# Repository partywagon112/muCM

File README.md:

# μCM

A small ESP32 based flexible controller, intended for Matter to control an RGB light or motor, but very very flexible. Based around ESP32-C6 for flexibility. Built to work in two contexts, in isolated locations where only power may be provided, up to 40V 3A, or as a PD powered dongle, up to 20V, 3A. 

Includes a 3V3 CAN driver for interacting with smaller devices, two pairs of half bridges allow driving servos, LEDs, or outputs more generally.

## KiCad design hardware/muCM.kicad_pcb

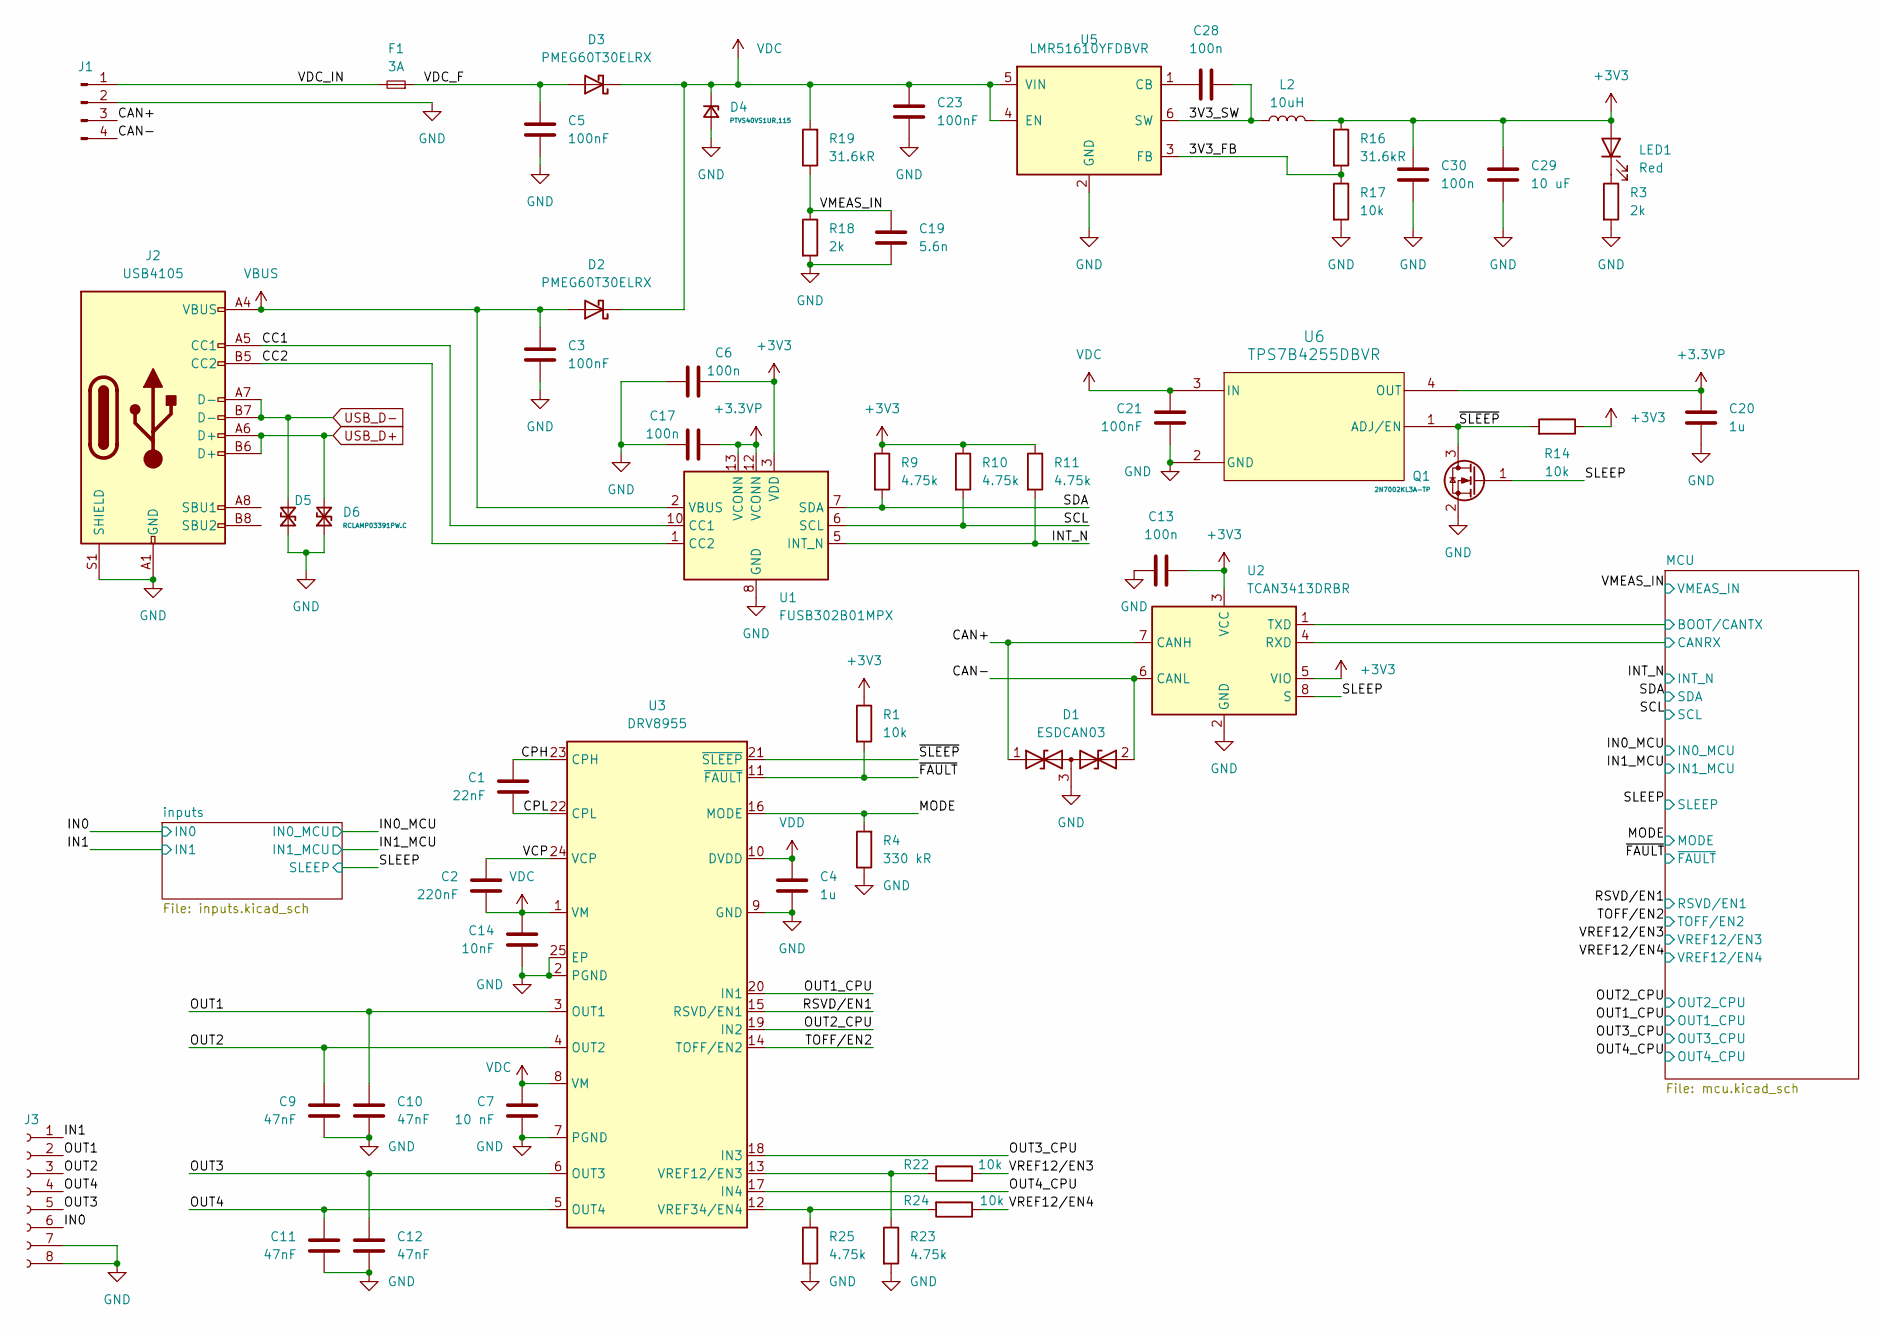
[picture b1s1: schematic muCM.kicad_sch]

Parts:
C1: 22nF; C_0603_1608Metric; MPN CL10B223KC8WPNC; DigiKey SPN 1276-CL10B223KC8WPNCCT-ND
C2: 220nF; C_0603_1608Metric; MPN HMK107C7224MAHTE; DigiKey SPN 587-5013-1-ND
C3, C5, C21, C23: 100nF; C_0603_1608Metric; MPN GCJ188R72A104KA01D; DigiKey SPN 490-13420-1-ND
C4, C20: 1u; C_0603_1608Metric; MPN GRT188R61H105KE13D; DigiKey SPN 490-12330-1-ND
C6, C13, C17, C28, C30: 100n; C_0402_1005Metric; MPN GCM155R71H104KE02J
C7: 10 nF; R_0603_1608Metric; MPN GCM188R71H103KA37D; DigiKey SPN 490-4778-1-ND
C9, C10, C11, C12: 47nF; C_0603_1608Metric; MPN CGA3E3X7S2A473K080AE; DigiKey SPN 445-173702-1-ND
C14: 10nF; C_0603_1608Metric; MPN CL10B103KC8WPNC; DigiKey SPN 1276-6556-1-ND
C19: 5.6n; C_0402_1005Metric; MPN GCM155R71H562KA55D; DigiKey SPN 490-GCM155R71H562KA55DCT-ND
C29: 10 uF; C_0603_1608Metric; MPN GRT188R61E106ME13D; DigiKey SPN 490-12323-1-ND
D1: ESDCAN03; DFN1006-3; MPN ESDCAN03-2BM3Y; DigiKey SPN 497-ESDCAN03-2BM3YCT-ND
D2, D3: PMEG60T30ELRX; Nexperia_CFP3_SOD-123W; MPN PMEG60T30ELRX; DigiKey SPN 1727-7806-1-ND
D4: PTVS40VS1UR,115; Nexperia_CFP3_SOD-123W; MPN PTVS40VS1UR,115; DigiKey SPN 1727-5873-1-ND
D5, D6: RCLAMP03391PW.C; D_SOD-882; MPN RCLAMP03391PW.C; DigiKey SPN 600-RCLAMP03391PW.CCT-ND
F1: 3A; Fuse_0805_2012Metric; MPN MFU0805FF03000P100; DigiKey SPN MFU08053.00CT-ND
J1: CDM806-04A-MP-F011-67; CUI_CDM806-04A-MP-F011-67; MPN CDM806-04A-MP-F011-67; DigiKey SPN 2223-CDM806-04A-MP-F011-67-ND
J2: USB4105; USB_C_Receptacle_GCT_USB4105-xx-A_16P_TopMnt_Horizontal; MPN USB4105-GF-A; DigiKey SPN 2073-USB4105-GF-ACT-ND
J3: CDM805-08A-FP-F011-67; CUI_CDM805-08A-FP-F011-67; MPN CDM805-08A-FP-F011-67; DigiKey SPN 2223-CDM805-08A-FP-F011-67-ND
L2: 10uH; L_1008_2520Metric; MPN SRN2510BTA-100M; DigiKey SPN 118-SRN2510BTA-100MCT-ND
LED1: Red; LED_0603_1608Metric; MPN 150060SS75020
Q1: 2N7002KL3A-TP; Diodes_DFN1006-3; MPN 2N7002KL3A-TP; DigiKey SPN 353-2N7002KL3A-TPCT-ND
R1, R14, R17, R22, R24: 10k; R_0402_1005Metric; MPN CR0402AFX-1002GAS; DigiKey SPN CR0402AFX-1002GASCT-ND
R3, R18: 2k; R_0402_1005Metric; MPN CR0402AFX-2001GAS
R4: 330 kR; R_0402_1005Metric; MPN CRGCQ0402F330K; DigiKey SPN A129657CT-ND
R9, R10, R11, R23, R25: 4.75k; R_0402_1005Metric; MPN CR0402AFX-4751GAS; DigiKey SPN CR0402AFX-4751GASCT-ND
R16, R19: 31.6kR; R_0402_1005Metric; MPN CRCW040231K6FKED; DigiKey SPN 541-31.6KLCT-ND
U1: FUSB302B01MPX; WQFN-14-1EP_2.5x2.5mm_P0.5mm_EP1.45x1.45mm; MPN FUSB302B01MPX; DigiKey SPN FUSB302B01MPXCT-ND
U2: TCAN3413DRBR; VSON-8-1EP_3x3mm_P0.65mm_EP1.6x2.4mm; MPN TCAN3413DRBR; DigiKey SPN 296-TCAN3413DRBRCT-ND
U3: DRV8955; VQFN-24-1EP_4x4mm_P0.5mm_EP2.45x2.45mm; MPN DRV8955PRGER; DigiKey SPN 296-DRV8955PRGERCT-ND
U5: LMR51610YFDBVR; SOT-23-6; MPN LMR51610YFDBVR; DigiKey SPN 296-LMR51610YFDBVRCT-ND
U6: TPS7B4255DBVR; SOT-23-5; MPN TPS7B4255DBVR; DigiKey SPN 296-TPS7B4255DBVRCT-ND

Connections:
+3.3VP: C17.1, C20.1, U1.12 (VCONN), U1.13 (VCONN), U6.4 (OUT); also elsewhere on the board
+3V3: C6.1, C13.2, C29.1, C30.1, L2.2, LED1.2 (A), R1.1, R9.1, R10.1, R11.1, R14.1, R16.1, U1.3 (VDD), U1.4 (VDD), U2.3 (VCC), U2.5 (VIO); also elsewhere on the board
/3V3_FB: R16.2, R17.1, U5.3 (FB)
/3V3_SW: C28.2, L2.1, U5.6 (SW)
/CAN+: D1.1 (A1), J1.3, U2.7 (CANH)
/CAN-: D1.2 (A2), J1.4, U2.6 (CANL)
/CC1: J2.A5 (CC1), U1.10 (CC1), U1.11 (CC1)
/CC2: J2.B5 (CC2), U1.1 (CC2), U1.14 (CC2)
/CPH: C1.1, U3.23 (CPH)
/CPL: C1.2, U3.22 (CPL)
/IN0: J3.6; also elsewhere on the board
/IN1: J3.1; also elsewhere on the board
/INT_N: R11.2, U1.5 (INT_N); also elsewhere on the board
/MCU/BOOT/CANTX: U2.1 (TXD); also elsewhere on the board
/MCU/CANRX: U2.4 (RXD); also elsewhere on the board
/MODE: R4.2, U3.16 (MODE); also elsewhere on the board
/OUT1: C10.1, J3.2, U3.3 (OUT1)
/OUT1_CPU: U3.20 (IN1); also elsewhere on the board
/OUT2: C9.1, J3.3, U3.4 (OUT2)
/OUT2_CPU: U3.19 (IN2); also elsewhere on the board
/OUT3: C12.1, J3.5, U3.6 (OUT3)
/OUT3_CPU: U3.18 (IN3); also elsewhere on the board
/OUT4: C11.1, J3.4, U3.5 (OUT4)
/OUT4_CPU: U3.17 (IN4); also elsewhere on the board
/RSVD/EN1: U3.15 (RSVD/EN1); also elsewhere on the board
/SCL: R10.2, U1.6 (SCL); also elsewhere on the board
/SDA: R9.2, U1.7 (SDA); also elsewhere on the board
/SLEEP: Q1.1 (G), U2.8 (S); also elsewhere on the board
/TOFF/EN2: U3.14 (TOFF/EN2); also elsewhere on the board
/VCP: C2.1, U3.24 (VCP)
/VDC_F: C5.1, D3.2 (A), F1.1
/VDC_IN: F1.2, J1.1
/VMEAS_IN: C19.1, R18.1, R19.1; also elsewhere on the board
/VREF12/EN3: R22.2; also elsewhere on the board
/VREF12/EN4: R24.1; also elsewhere on the board
/~FAULT: R1.2, U3.11 (~FAULT); also elsewhere on the board
/~SLEEP: Q1.3 (D), R14.2, U3.21 (~SLEEP), U6.1 (ADJ/EN)
GND: C3.2, C4.2, C5.2, C6.2, C7.2, C9.2, C10.2, C11.2, C12.2, C13.1, C14.2, C17.2, C19.2, C20.2, C21.2, C23.2, C29.2, C30.2, D1.3 (common), D4.2 (A), D5.1 (A1), D6.1 (A1), J1.2, J2.A1 (GND), J2.A12 (GND), J2.B1 (GND), J2.B12 (GND), J2.S1 (SHIELD), J3.7, J3.8, Q1.2 (S), R3.2, R4.1, R17.2, R18.2, R23.2, R25.2, U1.8 (GND), U1.9 (GND), U1.15 (GND), U2.2 (GND), U2.9, U3.2 (PGND), U3.7 (PGND), U3.9 (GND), U3.25 (EP), U5.2 (GND), U6.2 (GND); also elsewhere on the board
unnamed: LED1.1 (K), R3.1
unnamed: R22.1, R23.1, U3.13 (VREF12/EN3)
unnamed: R24.2, R25.1, U3.12 (VREF34/EN4)
unnamed: C28.1, U5.1 (CB)
USB_D+: D6.2 (A2), J2.A6 (D+), J2.B6 (D+); also elsewhere on the board
USB_D-: D5.2 (A2), J2.A7 (D-), J2.B7 (D-); also elsewhere on the board
VBUS: C3.1, D2.2 (A), J2.A4 (VBUS), J2.A9 (VBUS), J2.B4 (VBUS), J2.B9 (VBUS), U1.2 (VBUS)
VDC: C2.2, C7.1, C14.1, C21.1, C23.1, D2.1 (K), D3.1 (K), D4.1 (K), R19.2, U3.1 (VM), U3.8 (VM), U5.4 (EN), U5.5 (VIN), U6.3 (IN)
VDD: C4.1, U3.10 (DVDD)

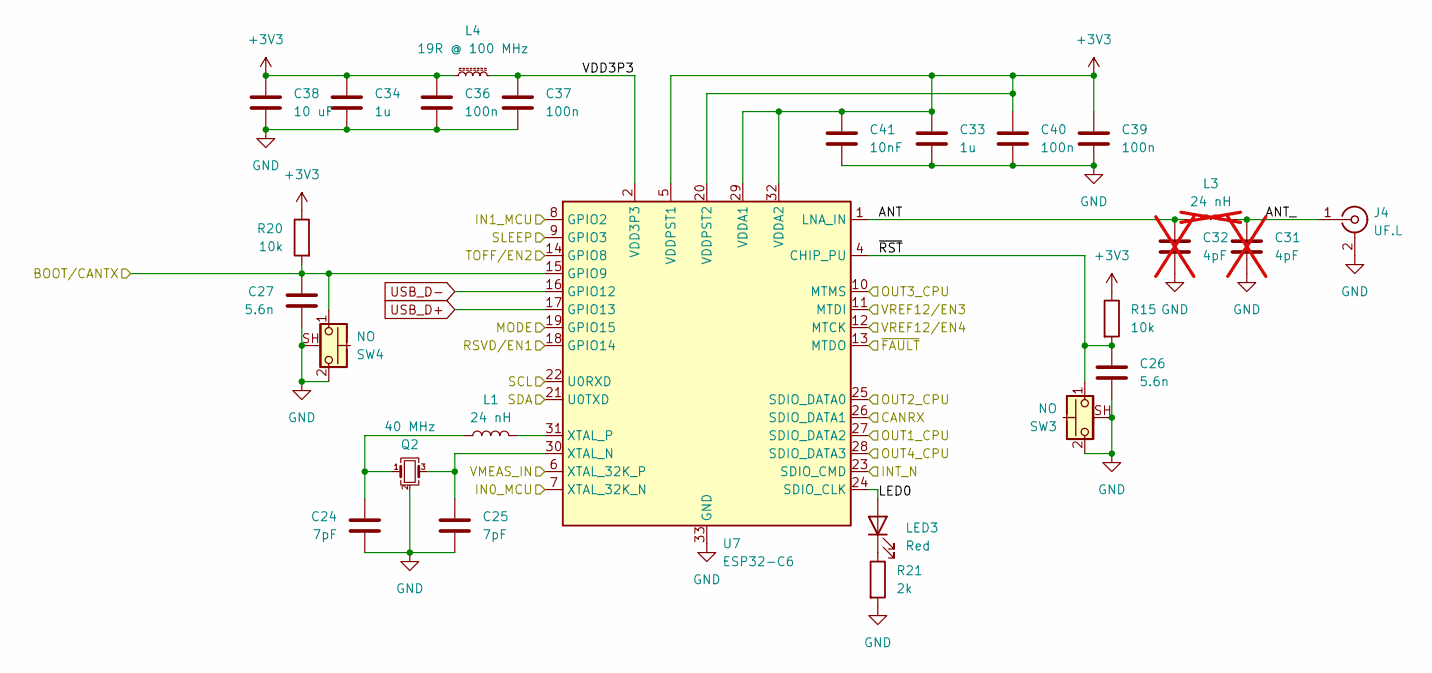
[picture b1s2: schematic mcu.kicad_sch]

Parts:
C24, C25: 7pF; C_0402_1005Metric; MPN GCM1555C1H7R0BA16D; DigiKey SPN 490-GCM1555C1H7R0BA16DCT-ND
C26, C27: 5.6n; C_0402_1005Metric; MPN GCM155R71H562KA55D; DigiKey SPN 490-GCM155R71H562KA55DCT-ND
C31, C32: 4pF; C_0402_1005Metric; MPN GCM1555C1H4R0BA16D; DigiKey SPN 490-GCM1555C1H4R0BA16DCT-ND; not fitted
C33, C34: 1u; C_0603_1608Metric; MPN GRT188R61H105KE13D; DigiKey SPN 490-12330-1-ND
C36, C37, C39, C40: 100n; C_0402_1005Metric; MPN GCM155R71H104KE02J
C38: 10 uF; C_0603_1608Metric; MPN GRT188R61E106ME13D; DigiKey SPN 490-12323-1-ND
C41: 10nF; C_0402_1005Metric; MPN GCM155R71H103KA55D; DigiKey SPN 490-4762-1-ND
J4: UF.L; U.FL_Hirose_U.FL-R-SMT-1_Vertical; MPN U.FL-R-SMT(10); DigiKey SPN H9161CT-ND
L1: 24 nH; L_0402_1005Metric; MPN MLG1005S24NJTD25; DigiKey SPN 445-16275-1-ND
L3: 24 nH; L_0402_1005Metric; MPN MLG1005S24NJTD25; DigiKey SPN 445-16275-1-ND; not fitted
L4: 19R @ 100 MHz; L_0402_1005Metric; MPN LI0402E190R-10; DigiKey SPN 240-LI0402E190R-10CT-ND
LED3: Red; LED_0603_1608Metric; MPN 150060SS75020
Q2: 40 MHz; Crystal_SMD_2016-4Pin_2.0x1.6mm; MPN XTL501100-M118-207; DigiKey SPN 3994-XTL501100-M118-207CT-ND
R15, R20: 10k; R_0402_1005Metric; MPN CR0402AFX-1002GAS; DigiKey SPN CR0402AFX-1002GASCT-ND
R21: 2k; R_0402_1005Metric; MPN CR0402AFX-2001GAS
SW3, SW4: NO; SW_Push_1P1T-SH_NO_CK_KMR2xxG; MPN KMR221G LFS; DigiKey SPN 401-1427-1-ND
U7: ESP32-C6; QFN-32-1EP_5x5mm_P0.5mm_EP3.7x3.7mm; MPN ESP32-C6FH4; DigiKey SPN 1904-ESP32-C6FH4CT-ND

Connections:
+3V3: C33.1, C34.1, C36.1, C38.1, C39.1, C40.1, C41.1, L4.1, R15.1, R20.1, U7.5 (VDDPST1), U7.20 (VDDPST2), U7.29 (VDDA1), U7.32 (VDDA2); also elsewhere on the board
/IN0_MCU: U7.7 (XTAL_32K_N); also elsewhere on the board
/IN1_MCU: U7.8 (GPIO2); also elsewhere on the board
/INT_N: U7.23 (SDIO_CMD); also elsewhere on the board
/MCU/ANT: C32.1, L3.1, U7.1 (LNA_IN)
/MCU/ANT_: C31.1, J4.1 (In), L3.2
/MCU/BOOT/CANTX: C27.1, R20.2, SW4.1, U7.15 (GPIO9); also elsewhere on the board
/MCU/CANRX: U7.26 (SDIO_DATA1); also elsewhere on the board
/MCU/LED0: LED3.2 (A), U7.24 (SDIO_CLK)
/MCU/~RST: C26.1, R15.2, SW3.1, U7.4 (CHIP_PU)
/MODE: U7.19 (GPIO15); also elsewhere on the board
/OUT1_CPU: U7.27 (SDIO_DATA2); also elsewhere on the board
/OUT2_CPU: U7.25 (SDIO_DATA0); also elsewhere on the board
/OUT3_CPU: U7.10 (MTMS); also elsewhere on the board
/OUT4_CPU: U7.28 (SDIO_DATA3); also elsewhere on the board
/RSVD/EN1: U7.18 (GPIO14); also elsewhere on the board
/SCL: U7.22 (U0RXD); also elsewhere on the board
/SDA: U7.21 (U0TXD); also elsewhere on the board
/SLEEP: U7.9 (GPIO3); also elsewhere on the board
/TOFF/EN2: U7.14 (GPIO8); also elsewhere on the board
/VMEAS_IN: U7.6 (XTAL_32K_P); also elsewhere on the board
/VREF12/EN3: U7.11 (MTDI); also elsewhere on the board
/VREF12/EN4: U7.12 (MTCK); also elsewhere on the board
/~FAULT: U7.13 (MTDO); also elsewhere on the board
GND: C24.2, C25.2, C26.2, C27.2, C31.2, C32.2, C33.2, C34.2, C36.2, C37.2, C38.2, C39.2, C40.2, C41.2, J4.2 (Ext), Q2.2 (G), Q2.4 (G), R21.2, SW3.2, SW3.SH (B), SW4.2, SW4.SH (B), U7.33 (GND); also elsewhere on the board
unnamed: C24.1, L1.1, Q2.1
unnamed: LED3.1 (K), R21.1
unnamed: C25.1, Q2.3, U7.30 (XTAL_N)
unnamed: L1.2, U7.31 (XTAL_P)
USB_D+: U7.17 (GPIO13); also elsewhere on the board
USB_D-: U7.16 (GPIO12); also elsewhere on the board
VDD3P3: C37.1, L4.2, U7.2 (VDD3P3), U7.3 (VDD3P3)

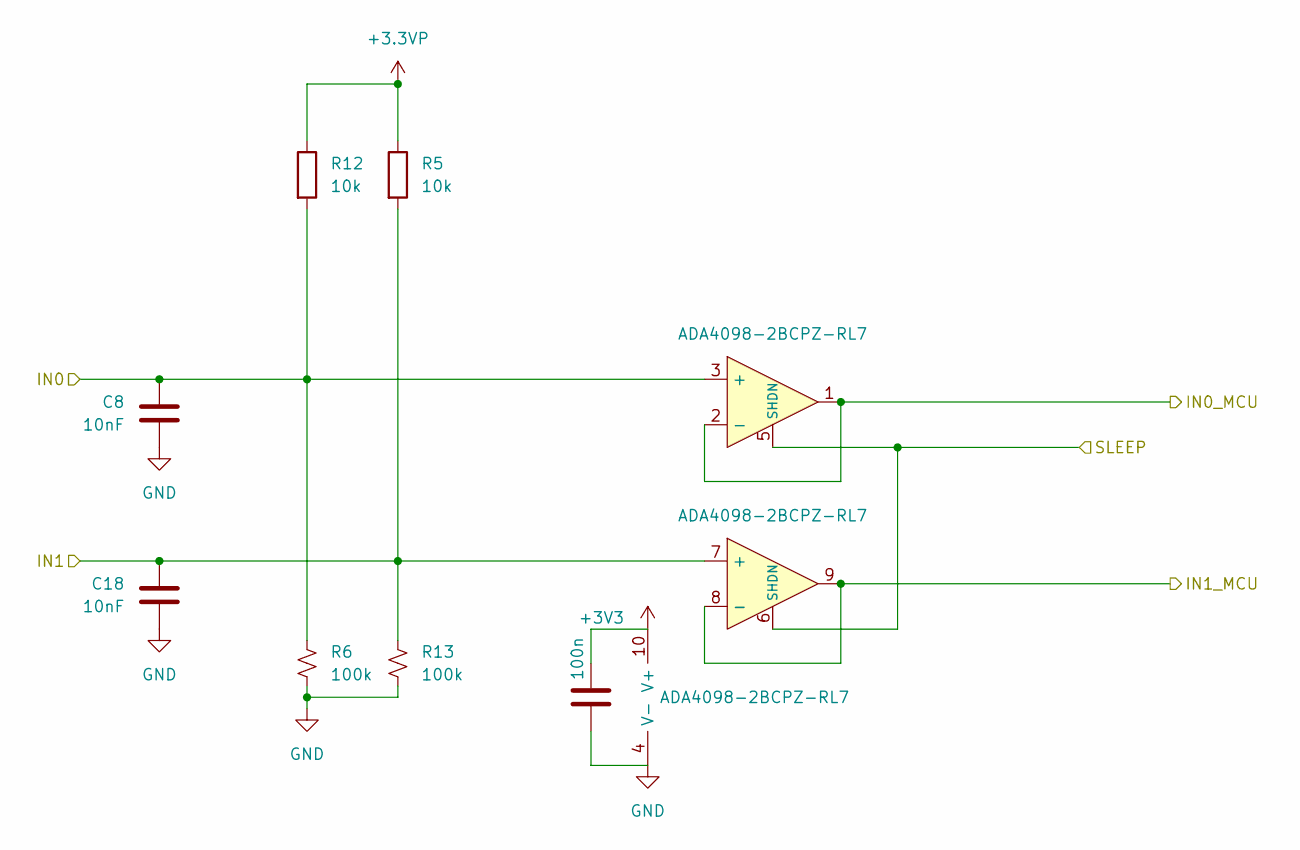
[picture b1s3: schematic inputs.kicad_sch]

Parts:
C8, C18: 10nF; C_0603_1608Metric; MPN CL10B103KC8WPNC; DigiKey SPN 1276-6556-1-ND
C22: 100n; C_0402_1005Metric; MPN GCM155R71H104KE02J
R5, R12: 10k; R_0402_1005Metric; MPN CR0402AFX-1002GAS; DigiKey SPN CR0402AFX-1002GASCT-ND
R6, R13: 100k; R_0402_1005Metric
U4: ADA4098-2BCPZ-RL7; LFCSP-WD-10-1EP_3x3mm_P0.5mm_EP1.64x2.38mm; MPN ADA4098-2BCPZ-RL7; DigiKey SPN 505-ADA4098-2BCPZ-RL7TR-ND

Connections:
+3.3VP: R5.1, R12.1; also elsewhere on the board
+3V3: C22.1, U4.10 (V+); also elsewhere on the board
/IN0: C8.1, R6.2, R12.2, U4.3 (+); also elsewhere on the board
/IN0_MCU: U4.1, U4.2 (-); also elsewhere on the board
/IN1: C18.1, R5.2, R13.2, U4.7 (+); also elsewhere on the board
/IN1_MCU: U4.8 (-), U4.9; also elsewhere on the board
/SLEEP: U4.5 (SHDN), U4.6 (SHDN); also elsewhere on the board
GND: C8.2, C18.2, C22.2, R6.1, R13.1, U4.4 (V-), U4.11 (V-); also elsewhere on the board

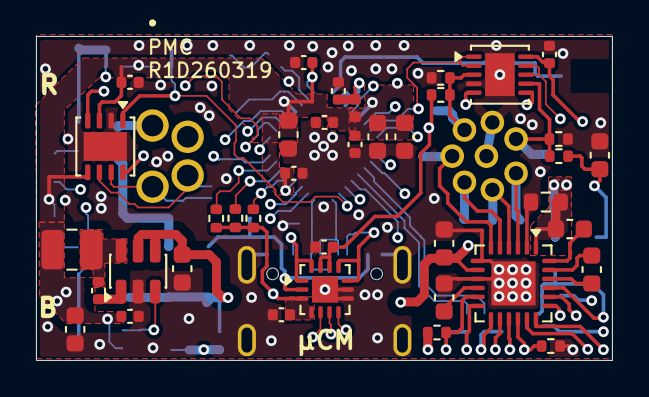
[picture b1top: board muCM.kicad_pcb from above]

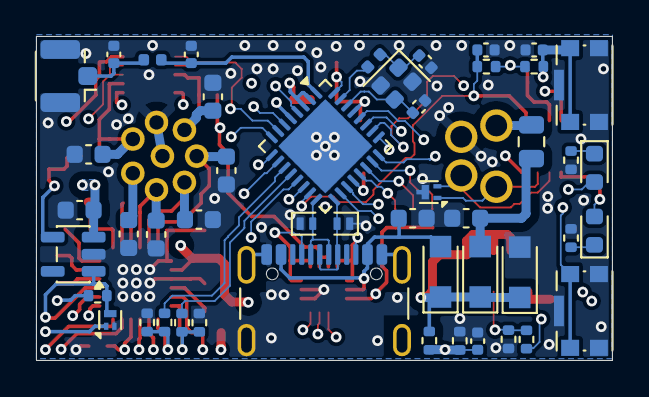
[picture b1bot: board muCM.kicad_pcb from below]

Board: 4 copper layers, 32.0 x 18.0 mm, 88 parts (48 on the bottom side), 58 nets.

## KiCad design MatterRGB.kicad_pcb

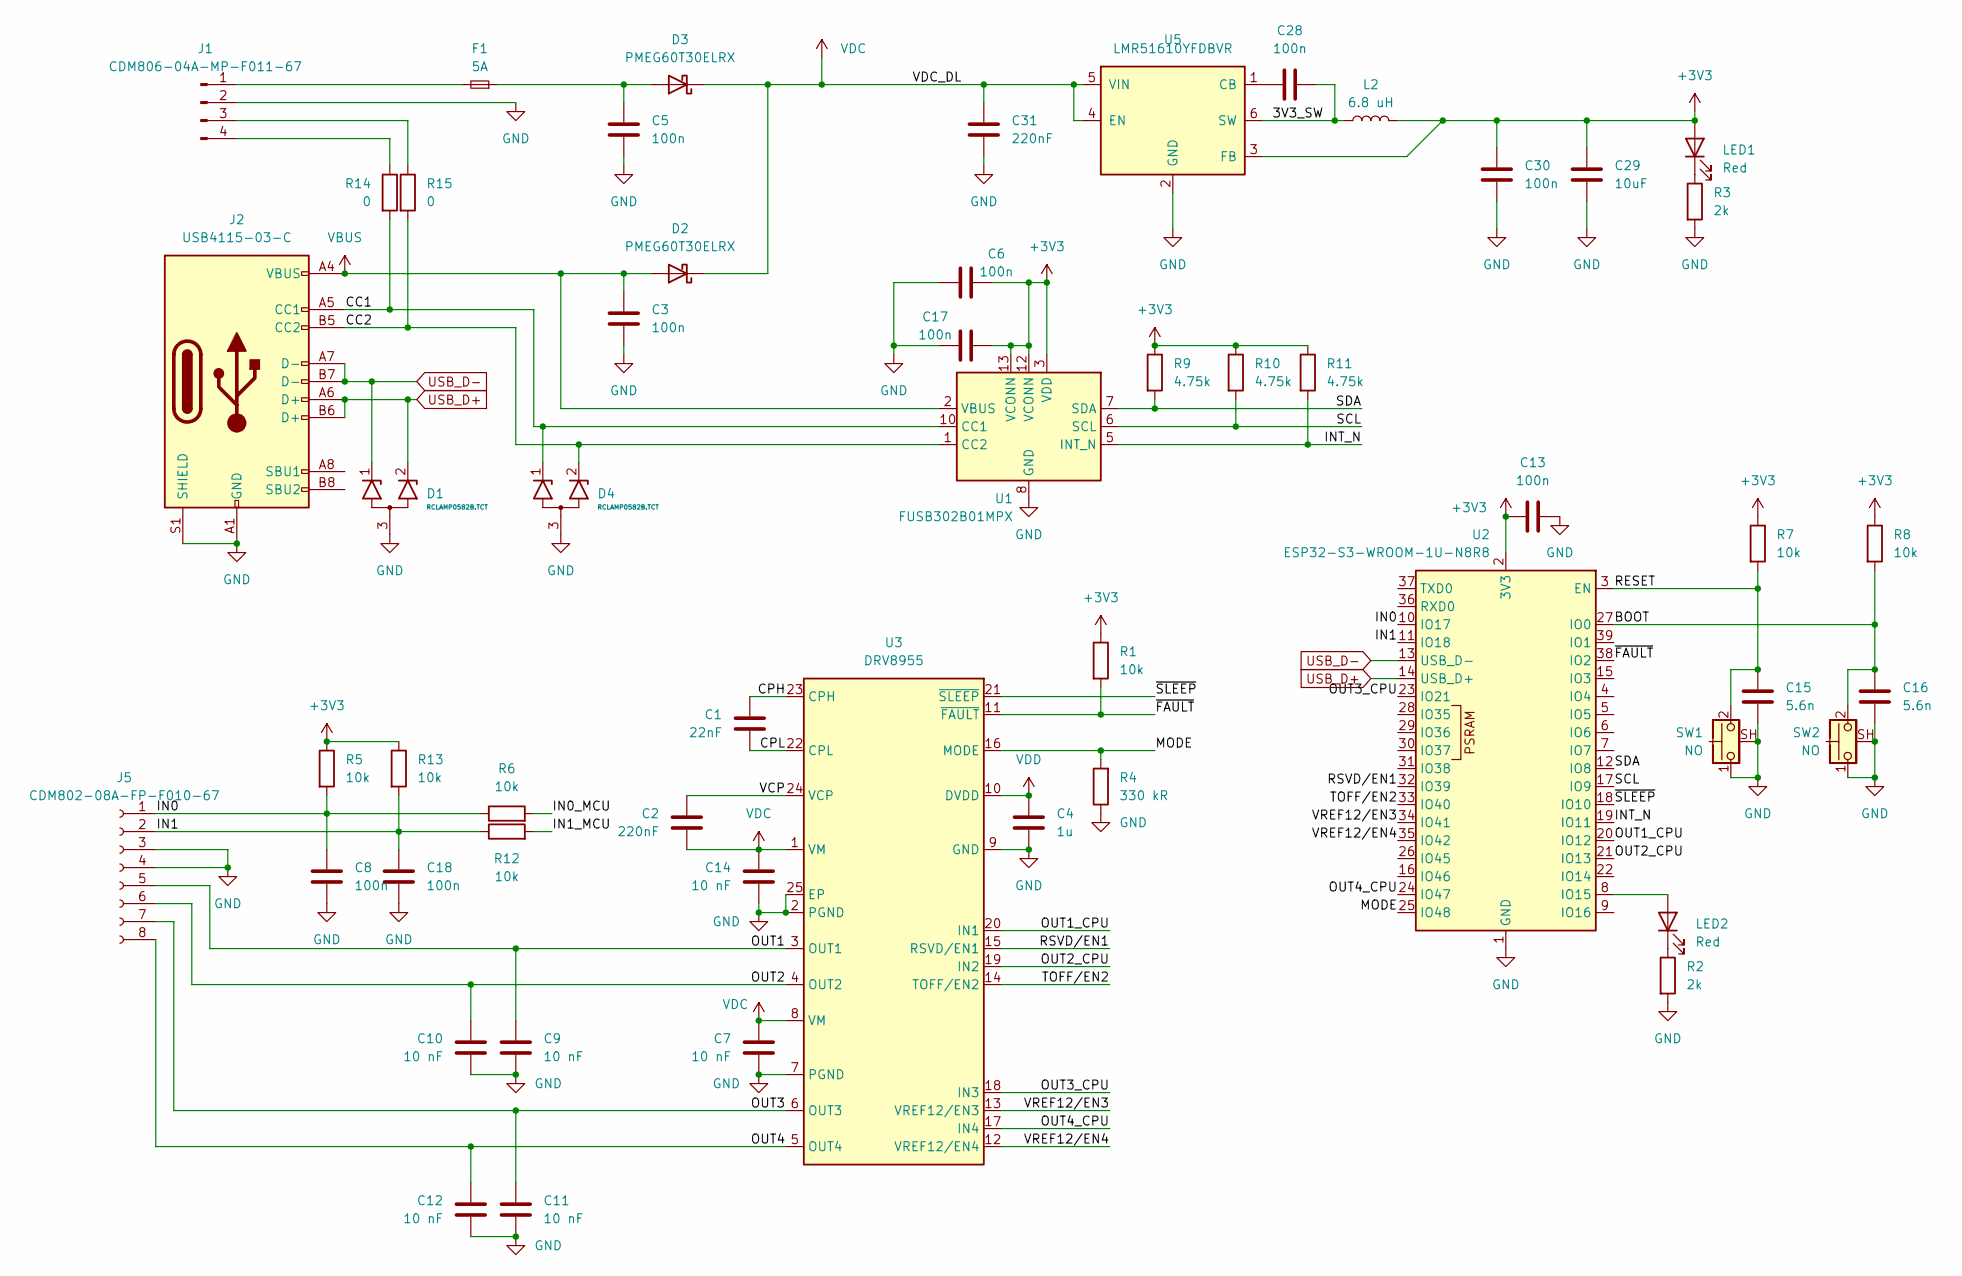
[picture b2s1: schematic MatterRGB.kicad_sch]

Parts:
C1: 22nF; C_0805_2012Metric; MPN KAS21KR71H223KU; DigiKey SPN 478-KAS21KR71H223KUCT-ND
C2: 220nF; C_0603_1608Metric; MPN GCM188R71H224KA64D; DigiKey SPN 490-5402-1-ND
C3, C5: 100n; C_0805_2012Metric; MPN KAS21KR72A104KU; DigiKey SPN 478-KAS21KR72A104KUTR-ND
C4: 1u; C_0603_1608Metric; MPN GRT188R61H105KE13D; DigiKey SPN 490-12330-1-ND
C6, C8, C13, C17, C18, C28, C30: 100n; C_0402_1005Metric; MPN GCM155R71H104KE02J
C7, C9, C10, C11, C12, C14: 10 nF; R_0603_1608Metric; MPN GCM188R71H103KA37D; DigiKey SPN 490-4778-1-ND
C15, C16: 5.6n; C_0402_1005Metric; MPN GCM155R71H562KA55D; DigiKey SPN 490-GCM155R71H562KA55DCT-ND
C29: 10uF; C_0805_2012Metric; MPN CGA4J1X7S1C106K125AE
C31: 220nF; C_0603_1608Metric; MPN GCM188R71H224KA64D
D1, D4: RCLAMP0582B.TCT; SOT-416; MPN RCLAMP0582B.TCT; DigiKey SPN RCLAMP0582B.TCTCT-ND
D2, D3: PMEG60T30ELRX; Nexperia_CFP3_SOD-123W; MPN PMEG60T30ELRX; DigiKey SPN 1727-7806-1-ND
F1: 5A; Fuse_0805_2012Metric; MPN MFU0805FF05000P100; DigiKey SPN MFU08055.00CT-ND
J1: CDM806-04A-MP-F011-67; CUI_CDM806-04A-MP-F011-67; MPN CDM806-04A-MP-F011-67; DigiKey SPN 2223-CDM806-04A-MP-F011-67-ND
J2: USB4115-03-C; USB_C_Receptacle_GCT_USB4115-03-C; MPN USB4115-03-C; DigiKey SPN 2073-USB4115-03-CCT-ND
J5: CDM802-08A-FP-F010-67; CUI_CDM802-08A-FP-F010-67; MPN CDM802-08A-FP-F010-67; DigiKey SPN 2223-CDM802-08A-FP-F010-67-ND
L2: 6.8 uH; L_1008_2520Metric; MPN SRN2510BTA-6R8M
LED1, LED2: Red; LED_0603_1608Metric; MPN 150060SS75020
R1, R5, R6, R7, R8, R12, R13: 10k; R_0402_1005Metric; MPN CR0402AFX-1002GAS; DigiKey SPN CR0402AFX-1002GASCT-ND
R2, R3: 2k; R_0402_1005Metric; MPN CR0402AFX-2001GAS
R4: 330 kR; R_0402_1005Metric; MPN CRGCQ0402F330K; DigiKey SPN A129657CT-ND
R9, R10, R11: 4.75k; R_0402_1005Metric; MPN CR0402AFX-4751GAS; DigiKey SPN CR0402AFX-4751GASCT-ND
R14, R15: 0; R_0402_1005Metric; MPN CR0402AJ/-000GLF; DigiKey SPN 118-CR0402AJ/-000GLFCT-ND
SW1, SW2: NO; SW_Push_1P1T-SH_NO_CK_KMR2xxG; MPN KMR221G LFS; DigiKey SPN 401-1427-1-ND
U1: FUSB302B01MPX; WQFN-14-1EP_2.5x2.5mm_P0.5mm_EP1.45x1.45mm; MPN FUSB302B01MPX; DigiKey SPN FUSB302B01MPXCT-ND
U2: ESP32-S3-WROOM-1U-N8R8; ESP32-S3-WROOM-1U; MPN ESP32-S3-WROOM-1U-N8R8; DigiKey SPN 1965-ESP32-S3-WROOM-1U-N8R8CT-ND
U3: DRV8955; VQFN-24-1EP_4x4mm_P0.5mm_EP2.45x2.45mm; MPN DRV8955PRGER; DigiKey SPN 296-DRV8955PRGERCT-ND
U5: LMR51610YFDBVR; SOT-23-6; MPN LMR51610YFDBVR; DigiKey SPN 296-LMR51610YFDBVRCT-ND

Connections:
+3V3: C6.1, C13.1, C17.1, C29.1, C30.1, L2.2, LED1.2 (A), R1.1, R5.1, R7.1, R8.1, R9.1, R10.1, R11.1, R13.1, U1.3 (VDD), U1.4 (VDD), U1.12 (VCONN), U1.13 (VCONN), U2.2 (3V3), U5.3 (FB)
/3V3_SW: C28.2, L2.1, U5.6 (SW)
/BOOT: C16.1, R8.2, SW2.2, U2.27 (IO0)
/CC1: D4.1 (K1), J2.A5 (CC1), R14.2, U1.10 (CC1), U1.11 (CC1)
/CC2: D4.2 (K2), J2.B5 (CC2), R15.2, U1.1 (CC2), U1.14 (CC2)
/CPH: C1.1, U3.23 (CPH)
/CPL: C1.2, U3.22 (CPL)
/IN0: C8.1, J5.1, R5.2, R6.1, U2.10 (IO17); also elsewhere on the board
/IN0_MCU: R6.2
/IN1: C18.1, J5.2, R12.1, R13.2, U2.11 (IO18); also elsewhere on the board
/IN1_MCU: R12.2
/INT_N: R11.2, U1.5 (INT_N), U2.19 (IO11)
/MODE: R4.2, U2.25 (IO48), U3.16 (MODE)
/OUT1: C9.1, J5.5, U3.3 (OUT1); also elsewhere on the board
/OUT1_CPU: U2.20 (IO12), U3.20 (IN1)
/OUT2: C10.1, J5.6, U3.4 (OUT2); also elsewhere on the board
/OUT2_CPU: U2.21 (IO13), U3.19 (IN2)
/OUT3: C11.1, J5.7, U3.6 (OUT3); also elsewhere on the board
/OUT3_CPU: U2.23 (IO21), U3.18 (IN3)
/OUT4: C12.1, J5.8, U3.5 (OUT4); also elsewhere on the board
/OUT4_CPU: U2.24 (IO47), U3.17 (IN4)
/RESET: C15.1, R7.2, SW1.2, U2.3 (EN)
/RSVD/EN1: U2.32 (IO39), U3.15 (RSVD/EN1)
/SCL: R10.2, U1.6 (SCL), U2.17 (IO9)
/SDA: R9.2, U1.7 (SDA), U2.12 (IO8)
/TOFF/EN2: U2.33 (IO40), U3.14 (TOFF/EN2)
/VCP: C2.1, U3.24 (VCP)
/VREF12/EN3: U2.34 (IO41), U3.13 (VREF12/EN3)
/VREF12/EN4: U2.35 (IO42), U3.12 (VREF12/EN4)
/~FAULT: R1.2, U2.38 (IO2), U3.11 (~FAULT)
/~SLEEP: U2.18 (IO10), U3.21 (~SLEEP)
GND: C3.2, C4.2, C5.2, C6.2, C7.2, C8.2, C9.2, C10.2, C11.2, C12.2, C13.2, C14.2, C15.2, C16.2, C17.2, C18.2, C29.2, C30.2, C31.2, D1.3 (A), D4.3 (A), J1.2, J2.A1 (GND), J2.A12 (GND), J2.B1 (GND), J2.B12 (GND), J2.S1 (SHIELD), J5.3, J5.4, R2.2, R3.2, R4.1, SW1.1, SW1.SH (B), SW2.1, SW2.SH (B), U1.8 (GND), U1.9 (GND), U1.15 (GND), U2.1 (GND), U2.40 (GND), U2.41 (GND), U3.2 (PGND), U3.7 (PGND), U3.9 (GND), U3.25 (EP), U5.2 (GND); also elsewhere on the board
unnamed: C5.1, D3.2 (A), F1.1
unnamed: F1.2, J1.1
unnamed: J1.3, R15.1
unnamed: J1.4, R14.1
unnamed: LED1.1 (K), R3.1
unnamed: LED2.2 (A), U2.8 (IO15)
unnamed: LED2.1 (K), R2.1
unnamed: C28.1, U5.1 (CB)
USB_D+: D1.2 (K2), J2.A6 (D+), J2.B6 (D+), U2.14 (USB_D+)
USB_D-: D1.1 (K1), J2.A7 (D-), J2.B7 (D-), U2.13 (USB_D-)
VBUS: C3.1, D2.2 (A), J2.A4 (VBUS), J2.A9 (VBUS), J2.B4 (VBUS), J2.B9 (VBUS), U1.2 (VBUS)
VDC: C2.2, C7.1, C14.1, C31.1, D2.1 (K), D3.1 (K), U3.1 (VM), U3.8 (VM), U5.4 (EN), U5.5 (VIN)
VDD: C4.1, U3.10 (DVDD)

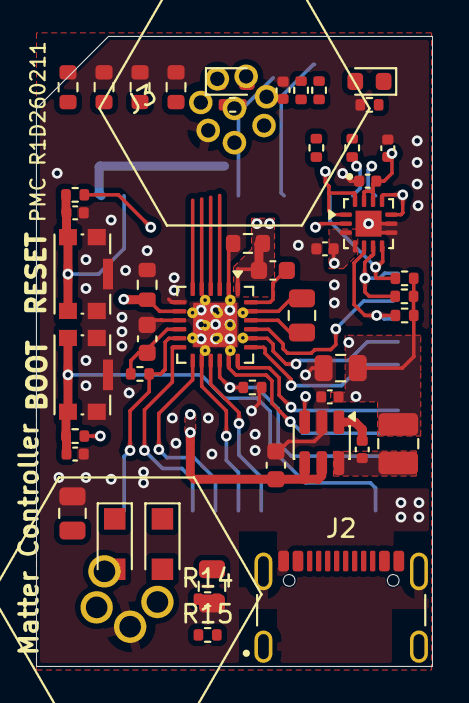
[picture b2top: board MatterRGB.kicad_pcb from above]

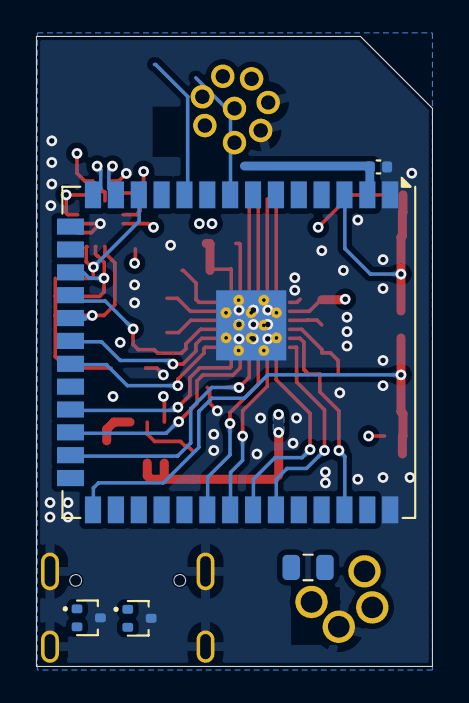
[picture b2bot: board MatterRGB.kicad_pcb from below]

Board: 4 copper layers, 22.0 x 35.0 mm, 54 parts (5 on the bottom side), 43 nets.

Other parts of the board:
J3: CDM805-08A-FP-F011-67; CUI_CDM805-08A-FP-F011-67

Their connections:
/IN0: J3.1; also elsewhere on the board
/IN1: J3.2; also elsewhere on the board
/OUT1: J3.5; also elsewhere on the board
/OUT2: J3.6; also elsewhere on the board
/OUT3: J3.7; also elsewhere on the board
/OUT4: J3.8; also elsewhere on the board
GND: J3.3, J3.4; also elsewhere on the board

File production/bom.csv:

Designator,Footprint,Quantity,Value,LCSC Part #
C1,0805,1,22nF,KAS21KR71H223KU
"C10, C11, C12, C14, C7, C9",0603,6,10 nF,GCM188R71H103KA37D
"C13, C17, C28, C30, C6, C8",0402,6,100n,GCM155R71H104KE02J
"C15, C16",0402,2,5.6n,GCM155R71H562KA55D
"C2, C31",0603,2,220nF,GCM188R71H224KA64D
C29,0805,1,10uF,CGA4J1X7S1C106K125AE
"C3, C5",0805,2,100n,KAS21KR72A104KU
C4,0603,1,1u,GRT188R61H105KE13D
D1,SOT-416,1,RCLAMP0582B.TCT,RCLAMP0582B.TCT
"D2, D3",Nexperia_CFP3_SOD-123W,2,PMEG60T30ELRX,PMEG60T30ELRX
F1,0805,1,5A,MFU0805FF05000P100
J1,USB_C_Receptacle_GCT_USB4105-xx-A_16P_TopMnt_Horizontal,1,USB4105,USB4105-GF-A
J2,JST_PH_S4B-PH-K_1x04_P2.00mm_Horizontal,1,S4B-PH-K-S,S4B-PH-K-S
J4,JST_XH_S2B-XH-A-1_1x02_P2.50mm_Horizontal,1,S2B-XH-A-1,S2B-XH-A-1
J5,JST_PH_S2B-PH-K_1x02_P2.00mm_Horizontal,1,S2B-PH-K-S,S2B-PH-K-S
L2,1008,1,6.8 uH,SRN2510BTA-6R8M
"LED1, LED2",0603,2,Red,150060SS75020
"R1, R5, R6, R7, R8",0402,5,10k,CR0402AFX-1002GAS
"R10, R11, R9",0402,3,4.75k,CR0402AFX-4751GAS
"R2, R3",0402,2,2k,CR0402AFX-2001GAS
R4,0402,1,330 kR,CRGCQ0402F330K
"SW1, SW2",SW_Push_1P1T-SH_NO_CK_KMR2xxG,2,NO,KMR221G LFS
U1,WQFN-14-1EP_2.5x2.5mm_P0.5mm_EP1.45x1.45mm,1,FUSB302B01MPX,FUSB302B01MPX
U2,ESP32-S3-WROOM-1,1,ESP32-S3-WROOM-1-N8R8,ESP32-S3-WROOM-1-N8R8
U3,VQFN-24-1EP_4x4mm_P0.5mm_EP2.45x2.45mm,1,DRV8955,DRV8955PRGER
U5,SOT-23-6,1,LMR50410Y3FQDBVRQ1,LMR50410Y3FQDBVRQ1

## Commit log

2025-10-01 Added image
2025-10-30 Added stencil
2025-11-06 started fw
2025-11-06 Lots of other stuff
2025-11-11 fixed typos in driver
2026-02-10 Added new connector/mounting strategy
2026-03-02 Last version before c6 conversion
2026-03-18 Finished draft layout of muCM update.
2026-03-19 removed backups
2026-03-19 cleanup
2026-03-19 Rename project to μCM and refine description
    Updated project name and enhanced description for clarity.
2026-03-19 added pd conf from rbaron
2026-03-19 Enhance README with detailed controller specifications
    Expanded description of the μCM controller's capabilities and power contexts.
